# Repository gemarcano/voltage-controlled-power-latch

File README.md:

# Voltage controlled power latch

This circuit was designed to monitor the main voltage and trigger an enable signal when it is reached, which is then latched and won't disengage until the transistors reset, or a shutdown signal is applied.

The latch circuit was borrowed from https://github.com/lab11/monjolo project, specifically the gecko\_power\_supply revision E hardware. Parts were upgraded to use ones that draw even less power than the ones used in the monjolo project.

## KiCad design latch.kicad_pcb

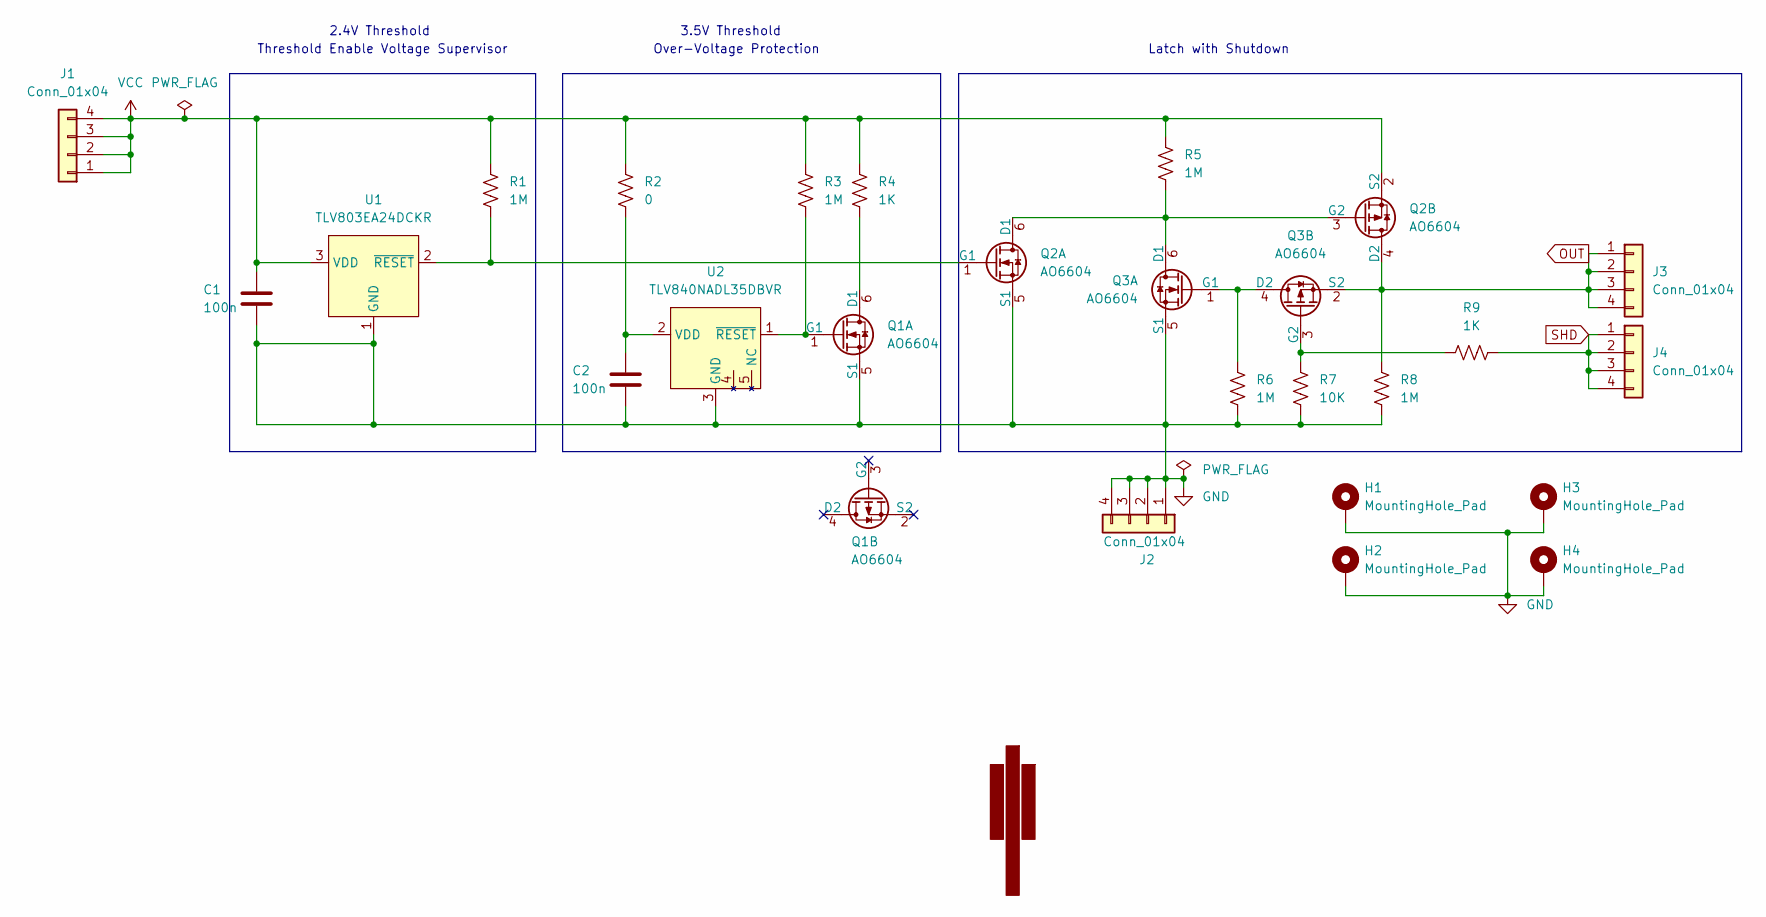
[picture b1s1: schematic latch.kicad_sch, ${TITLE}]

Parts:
C1, C2: 100n; C_0603_1608Metric_Pad1.08x0.95mm_HandSolder
G1: LOGO; smaller_logo
H1, H2, H3, H4: MountingHole_Pad; MountingHole_3.2mm_M3_Pad_Via
J1, J2, J3, J4: Conn_01x04; PinHeader_1x04_P2.54mm_Vertical
Q1, Q2, Q3: AO6604; SOT-457_Handsolder
R1, R3, R5, R6, R8: 1M; R_0603_1608Metric_Pad0.98x0.95mm_HandSolder
R2: 0; R_0603_1608Metric_Pad0.98x0.95mm_HandSolder
R4, R9: 1K; R_0603_1608Metric_Pad0.98x0.95mm_HandSolder
R7: 10K; R_0603_1608Metric_Pad0.98x0.95mm_HandSolder
U1: TLV803EA24DCKR; SOT-323_SC-70_Handsoldering
U2: TLV840NADL35DBVR; SOT-23-5_HandSoldering

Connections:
GND: C1.2, C2.2, H1.1, H2.1, H3.1, H4.1, J2.1, J2.2, J2.3, J2.4, Q1.5 (S1), Q2.5 (S1), Q3.5 (S1), R6.2, R7.2, R8.2, U1.1 (GND), U2.3 (GND)
unnamed: C2.1, R2.1, U2.2 (VDD)
unnamed: Q1.1 (G1), R3.2, U2.1 (~RESET)
unnamed: Q1.6 (D1), R4.2
unnamed: Q2.1 (G1), R1.1, U1.2 (~RESET)
unnamed: Q2.3 (G2), Q2.6 (D1), Q3.6 (D1), R5.2
unnamed: Q3.1 (G1), Q3.4 (D2), R6.1
unnamed: Q3.3 (G2), R7.1, R9.1
OUT: J3.1, J3.2, J3.3, J3.4, Q2.4 (D2), Q3.2 (S2), R8.1
SHD: J4.1, J4.2, J4.3, J4.4, R9.2
VCC: C1.1, J1.1, J1.2, J1.3, J1.4, Q2.2 (S2), R1.2, R2.2, R3.1, R4.1, R5.1, U1.3 (VDD)

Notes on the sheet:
Threshold Enable Voltage Supervisor
Over-Voltage Protection
3.5V Threshold
Latch with Shutdown
2.4V Threshold

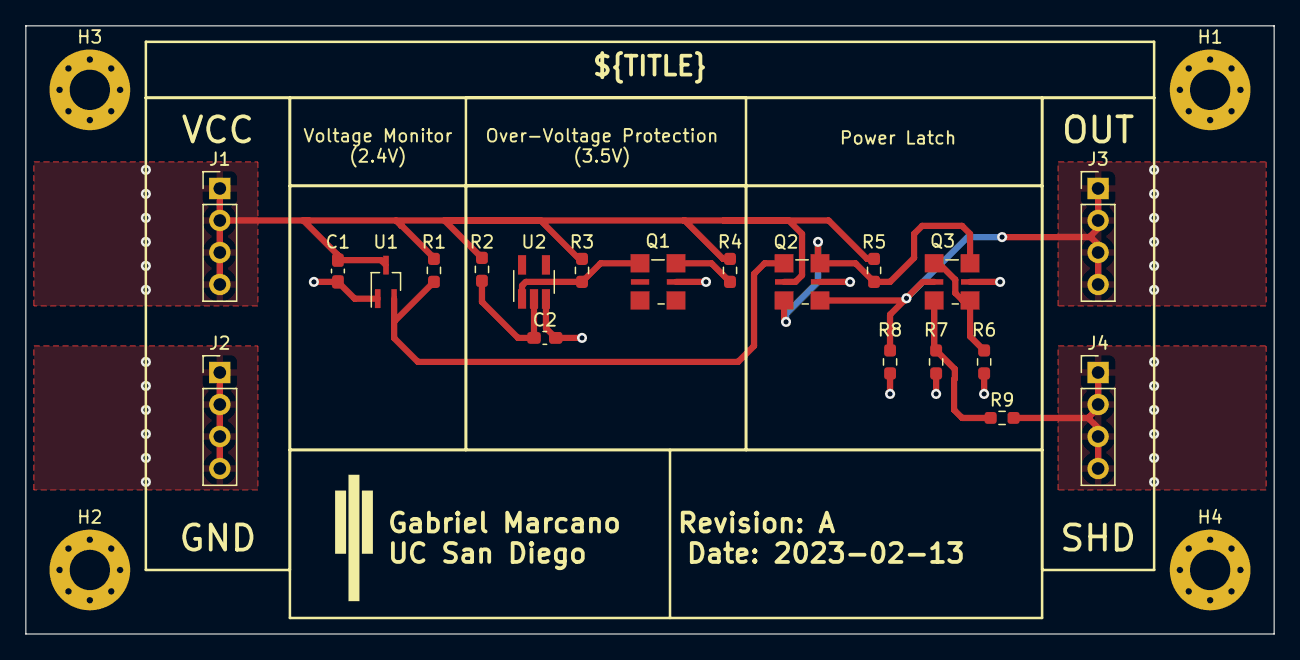
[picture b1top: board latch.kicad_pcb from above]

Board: 2 copper layers, 99.1 x 48.3 mm, 25 parts (0 on the bottom side), 11 nets.

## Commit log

2023-04-12 Add basic readme
    - Give credit to lab11 for the latch circuit
2023-06-13 Save project with latest KiCAD
    - Apparently opening the project with latest KiCAD and rendering a few
    things made modifications to the project-- looks mostly settings
    related, nothing functional?
2023-06-13 Upload schematics and PCB artifacts
